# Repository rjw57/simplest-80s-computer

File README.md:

# Experimental repo for retro computing

This is my rough scratch repo where I keep experiments to do with desiging 80s
computer peripherals. It is not in any sensible shape to be used by others yet,
apologies.

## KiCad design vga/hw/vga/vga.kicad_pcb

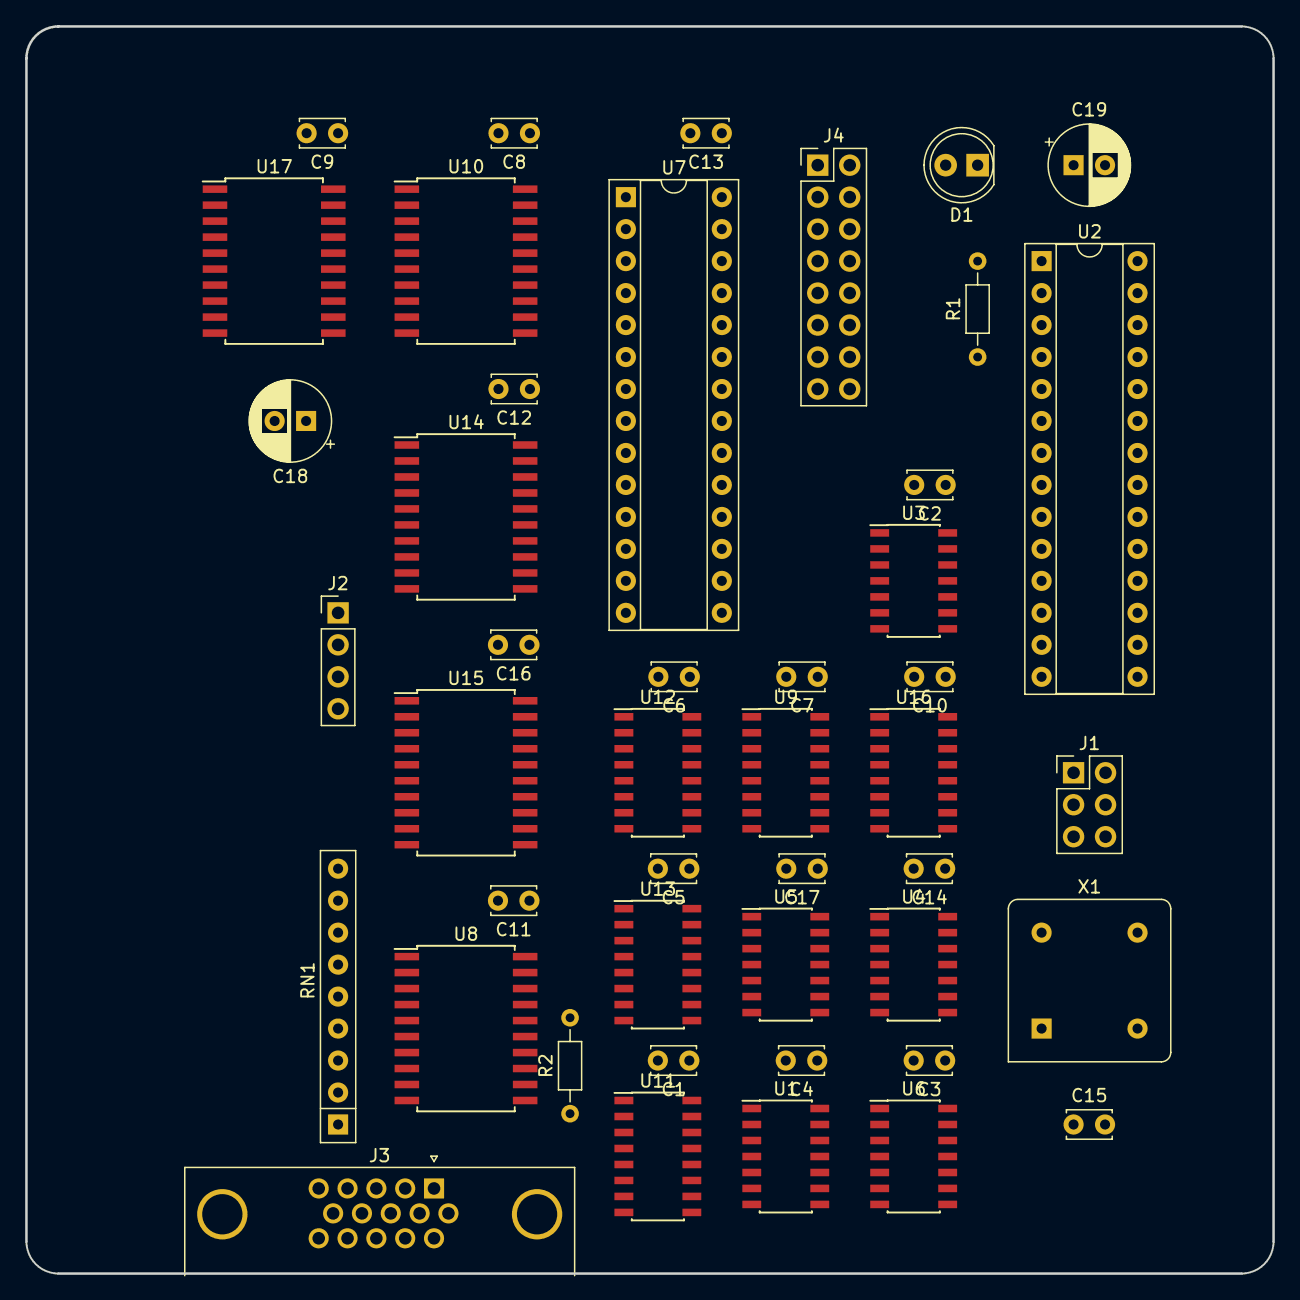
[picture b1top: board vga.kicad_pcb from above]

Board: 2 copper layers, 99.1 x 99.1 mm, 45 parts (0 on the bottom side), 81 nets, no tracks yet.

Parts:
C1, C2, C3, C4, C5, C6, C7, C8, C9, C10, C11, C12, C13, C14, C15, C16, C17: 100n; C_Disc_D3.4mm_W2.1mm_P2.50mm
C18: 10µ; CP_Radial_D6.3mm_P2.50mm
C19: 100µ; CP_Radial_D6.3mm_P2.50mm
D1: LED; LED_D5.0mm
J1: ISP; PinHeader_2x03_P2.54mm_Vertical
J2: PWR; PinHeader_1x04_P2.54mm_Vertical
J3: VGA; DSUB-15-HD_Female_Horizontal_P2.29x1.98mm_EdgePinOffset3.03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
J4: BUS; PinHeader_2x08_P2.54mm_Vertical
R1: 470R; R_Axial_DIN0204_L3.6mm_D1.6mm_P7.62mm_Horizontal
R2: 100R; R_Axial_DIN0204_L3.6mm_D1.6mm_P7.62mm_Horizontal
RN1: R_Network08; R_Array_SIP9
U1, U5, U6: 74HC74; SOIC-14_3.9x8.7mm_P1.27mm
U2: ATmega328-PU; DIP-28_W7.62mm_Socket
U3: 74HC00; SOIC-14_3.9x8.7mm_P1.27mm
U4: 74HC04; SOIC-14_3.9x8.7mm_P1.27mm
U7: CY7C199; DIP-28_W7.62mm_Socket
U8: 74HC245; SOIC-20W_7.5x12.8mm_P1.27mm
U9: 74HC161; SOIC-16_3.9x9.9mm_P1.27mm
U10, U14, U15, U17: 74HC574; SOIC-20W_7.5x12.8mm_P1.27mm
U11: 74HC166; SOIC-16_3.9x9.9mm_P1.27mm
U12, U13: 74HC590; SOIC-16_3.9x9.9mm_P1.27mm
U16: 74LS138; SOIC-16_3.9x9.9mm_P1.27mm
X1: DOTCLK; Oscillator_DIP-8

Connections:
+5V: C1.1, C2.1, C3.1, C4.1, C5.1, C6.1, C7.1, C8.1, C9.1, C10.1, C11.1, C12.1, C13.1, C14.1, C15.1, C16.1, C17.1, C18.1, C19.1, D1.2, J1.2, J2.1, J2.4, J4.2, R1.1, U1.1, U1.4, U1.10, U1.13, U1.14, U2.7, U2.20, U2.21, U3.14, U4.14, U5.1, U5.4, U5.10, U5.14, U6.1, U6.4, U6.10, U6.12, U6.14, U7.28, U8.20, U9.3, U9.6, U9.7, U9.10, U9.16, U10.20, U11.9, U11.16, U12.16, U13.16, U14.20, U15.20, U16.6, U16.16, U17.20, X1.1, X1.8
/A0: J4.4, U16.1
/A1: J4.6, U16.2
/C0: U7.21, U10.19, U12.15
/C1: U7.23, U10.18, U12.1
/C2: U7.24, U10.17, U12.2
/C3: U7.25, U10.16, U12.3
/C4: U7.26, U10.15, U12.4
/C5: U7.1, U10.14, U12.5
/CDOT0: U5.11, U9.14
/CDOT1: U5.3, U9.13
/CDOT2: U5.2, U9.12
/D0: J4.1, U10.2, U14.2, U15.2, U17.19
/D1: J4.3, U10.3, U14.3, U15.3, U17.18
/D2: J4.5, U10.4, U14.4, U15.4, U17.17
/D3: J4.7, U10.5, U14.5, U15.5, U17.16
/D4: J4.9, U10.6, U14.6, U15.6, U17.15
/D5: J4.11, U10.7, U14.7, U15.7, U17.14
/D6: J4.13, U10.8, U14.8, U15.8, U17.13
/D7: J4.15, U10.9, U14.9, U15.9, U17.12
/DOTCLK: U1.3, U4.6, U9.2, U11.7, U12.13, U13.13
/EXTEN: U3.2, U5.6, U5.13, U6.3, U12.14, U13.14
/EXTWREN: U3.5, U5.9
/HSYNC: J3.13, U4.2
/MCUCLK: U1.5, U2.9
/MISO: J1.1, U2.18
/MOSI: J1.4, U2.17
/R0: U7.2, U10.13, U12.7
/R1: U7.3, U10.12, U13.15
/R2: U7.4, U13.1, U14.19
/R3: U7.5, U13.2, U14.18
/R4: U7.6, U13.3, U14.17
/R5: U7.7, U13.4, U14.16
/R6: U7.8, U13.5, U14.15
/R7: U7.9, U13.6, U14.14
/R8: U7.10, U13.7, U14.13
/SCK: J1.3, U2.19
/V0: RN1.9, U8.2, U11.14
/V1: RN1.8, U8.3, U11.12
/V2: RN1.7, U8.4, U11.11
/V3: RN1.6, U8.5, U11.10
/V4: RN1.5, U8.6, U11.5
/V5: RN1.4, U8.7, U11.4
/V6: RN1.3, U8.8, U11.3
/V7: RN1.2, U8.9, U11.2
/VD0: U7.11, U8.18, U15.19, U17.2
/VD1: U7.12, U8.17, U15.18, U17.3
/VD2: U7.13, U8.16, U15.17
/VD3: U7.15, U8.15, U15.16
/VD4: U7.16, U8.14, U15.15, U17.6
/VD5: U7.17, U8.13, U15.14, U17.7
/VD6: U7.18, U8.12, U15.13, U17.8
/VD7: U7.19, U8.11, U15.12, U17.9
/VRAMOE: U3.3, U4.9, U15.1
/VRAMWREN: U3.1, U3.4, U6.5
/VSYNC: J3.14, U4.4
/WRPENDING: U6.2, U6.9
/~CSTART: U9.9, U9.11, U11.15, U12.11
/~EXTEN: U5.5, U10.1, U14.1
/~EXTWREN: U5.8, U5.12, U17.11
/~HSYNC: U1.11, U2.11, U4.1
/~ISPRST: J1.5, R1.2, U2.1
/~RD: J4.8, U17.1
/~RSTCOUNT: U3.8, U9.1, U12.10, U13.10
/~VIS: U2.5, U8.19, U12.12
/~VRAMOE: U4.8, U7.22
/~VRAMWE: U3.6, U7.27
/~VRAMWREN: U6.6, U6.13
/~VSYNC: U1.12, U2.16, U3.10, U4.3
/~WR: J4.10, U16.5
/~WRDATA: U6.11, U15.11, U16.13
/~WRHADDR: U14.11, U16.14
/~WRLADDR: U10.11, U16.15
GND: C1.2, C2.2, C3.2, C4.2, C5.2, C6.2, C7.2, C8.2, C9.2, C10.2, C11.2, C12.2, C13.2, C14.2, C15.2, C16.2, C17.2, C18.2, C19.2, J1.6, J2.2, J2.3, J3.0, J3.5, J3.6, J3.7, J3.8, J3.9, J3.10, J4.12, J4.14, J4.16, RN1.1, U1.7, U2.8, U2.22, U3.7, U4.7, U5.7, U6.7, U7.14, U7.20, U8.1, U8.10, U9.4, U9.5, U9.8, U10.10, U11.1, U11.6, U11.8, U12.8, U13.8, U13.12, U14.10, U15.10, U16.3, U16.4, U16.8, U17.10, X1.4
unnamed: D1.1, U2.2
unnamed: J3.1, J3.2, J3.3, R2.1
unnamed: R2.2, U11.13
unnamed: U1.2, U1.6
unnamed: U1.8, U3.9
unnamed: U4.5, X1.5
unnamed: U12.9, U13.11

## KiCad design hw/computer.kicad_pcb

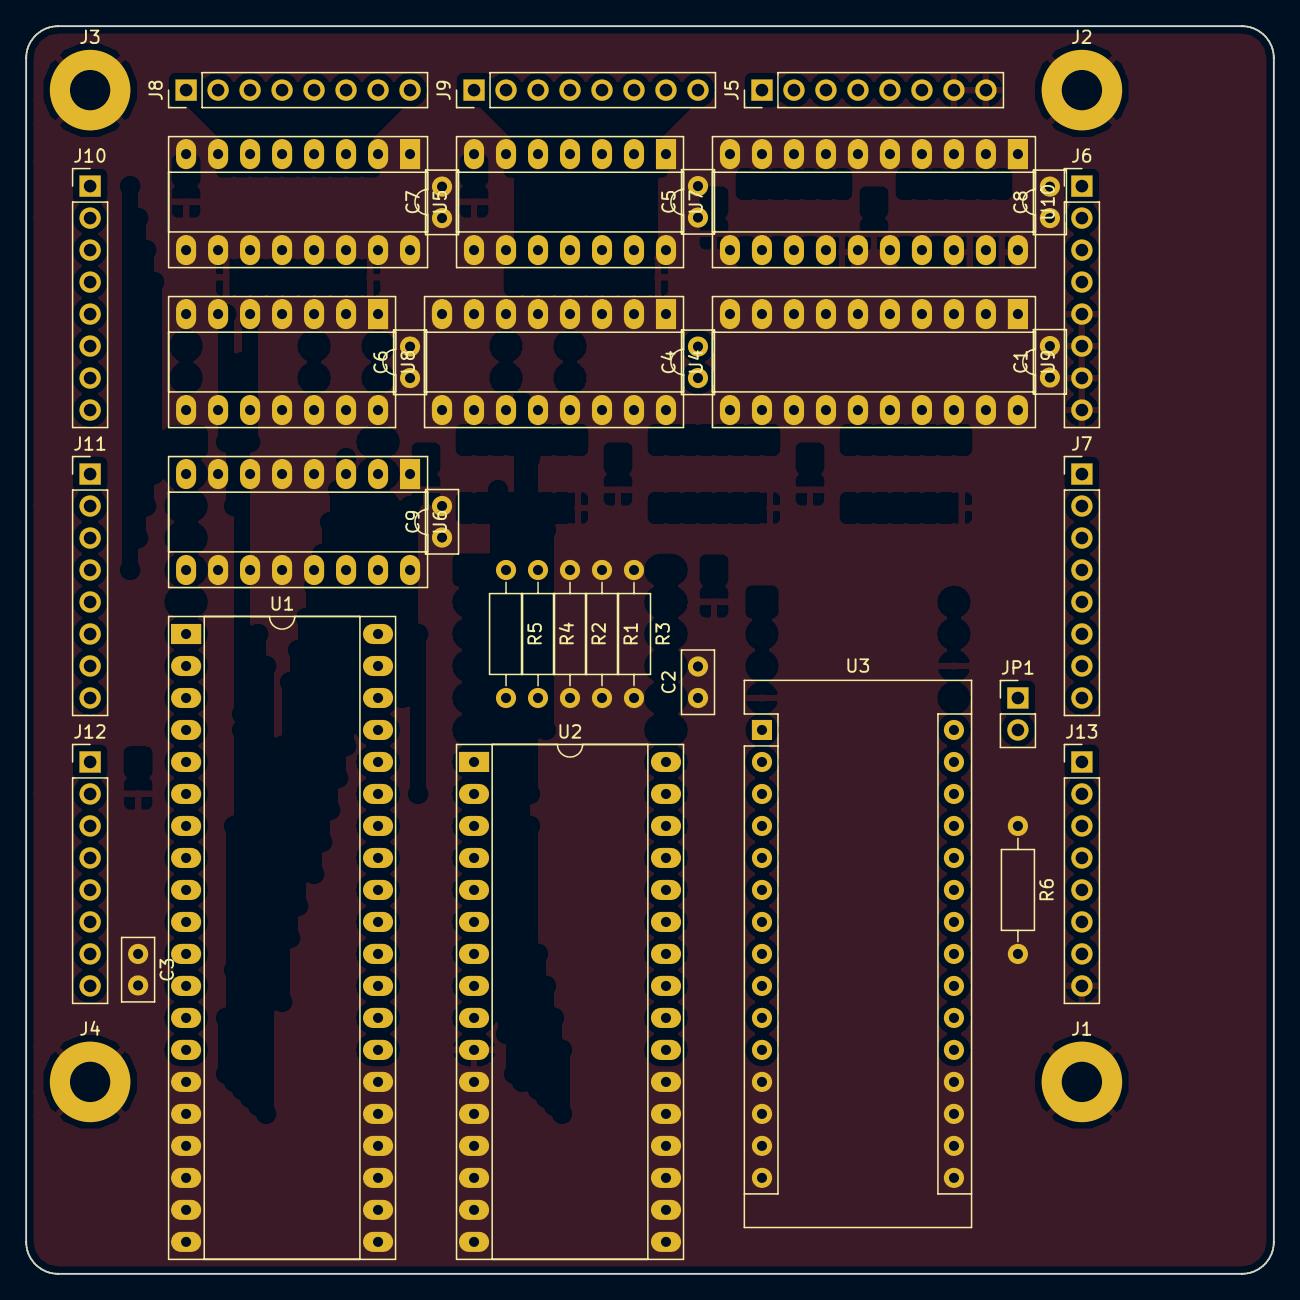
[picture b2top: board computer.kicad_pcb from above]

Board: 2 copper layers, 99.1 x 99.1 mm, 39 parts (0 on the bottom side), 71 nets, no tracks yet.

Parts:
C1, C2, C3, C4, C5, C6, C7, C8, C9: 100n; C_Disc_D5.0mm_W2.5mm_P2.50mm
J1, J2, J3, J4: MOUNT; MountingHole_3.2mm_M3_Pad
J5: POWER; Pin_Header_Straight_1x08_Pitch2.54mm
J6: PORTA; Pin_Header_Straight_1x08_Pitch2.54mm
J7: PORTB; Pin_Header_Straight_1x08_Pitch2.54mm
J8: ADDR2; Pin_Header_Straight_1x08_Pitch2.54mm
J9: ADDR1; Pin_Header_Straight_1x08_Pitch2.54mm
J10: DATA; Pin_Header_Straight_1x08_Pitch2.54mm
J11: CPU1; Pin_Header_Straight_1x08_Pitch2.54mm
J12: CPU2; Pin_Header_Straight_1x08_Pitch2.54mm
J13: NANO; Pin_Header_Straight_1x08_Pitch2.54mm
JP1: NANO PWR; Pin_Header_Straight_1x02_Pitch2.54mm
R1, R2, R3, R4, R5, R6: 330R; R_Axial_DIN0207_L6.3mm_D2.5mm_P10.16mm_Horizontal
U1: Z84C00; DIP-40_W15.24mm_Socket_LongPads
U2: AS6C4008; DIP-32_W15.24mm_Socket_LongPads
U3: Nano; Arduino_Nano
U4, U5, U6: 74HC595; DIP-16_W7.62mm_Socket_LongPads
U7: 74HC30; DIP-14_W7.62mm_Socket_LongPads
U8: 74HC27; DIP-14_W7.62mm_Socket_LongPads
U9, U10: 74HC573; DIP-20_W7.62mm_Socket_LongPads

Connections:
/A0: J9.8, U1.30, U2.12, U4.15, U7.1
/A1: J9.7, U1.31, U2.11, U4.1, U7.2
/A2: J9.6, U1.32, U2.10, U4.2, U7.3
/A3: J9.5, U1.33, U2.9, U4.3, U7.4
/A4: J9.4, U1.34, U2.8, U4.4, U7.5
/A5: J9.3, U1.35, U2.7, U4.5, U7.6
/A6: J9.2, U1.36, U2.6, U4.6, U7.11
/A7: J9.1, U1.37, U2.5, U4.7, U7.12
/A8: J8.8, U1.38, U2.4, U5.15
/A9: J8.7, U1.29, U2.3, U5.1
/A10: J8.6, U1.40, U2.25, U5.2
/A11: J8.5, U1.1, U2.23, U5.3
/A12: J8.4, U1.2, U2.26, U5.4
/A13: J8.3, U1.3, U2.27, U5.5
/A14: J8.2, U1.4, U2.28, U5.6
/A15: J8.1, U1.5, U2.31, U5.7
/Arduino/ARCLK: U3.15, U4.12, U5.12, U6.12
/Arduino/ASCLK: U3.16, U4.11, U5.11, U6.11
/Arduino/ASDA: U3.14, U4.14
/Arduino/~AOE: R6.2, U3.12, U4.13, U5.13, U6.13
/CLK: J12.7, U1.6, U3.11
/D0: J10.1, U1.14, U2.15, U3.19, U9.19, U10.2
/D1: J10.2, U1.15, U2.14, U3.20, U9.18, U10.3
/D2: J10.3, U1.12, U2.13, U3.21, U9.17, U10.4
/D3: J10.4, U1.8, U2.17, U3.22, U9.16, U10.5
/D4: J10.5, U1.7, U2.18, U3.23, U9.15, U10.6
/D5: J10.6, U1.9, U2.19, U3.24, U9.14, U10.7
/D6: J10.7, U1.10, U2.20, U3.9, U9.13, U10.8
/D7: J10.8, U1.13, U2.21, U3.10, U9.12, U10.9
/IO Ports/PA0: J6.1, U10.19
/IO Ports/PA1: J6.2, U10.18
/IO Ports/PA2: J6.3, U10.17
/IO Ports/PA3: J6.4, U10.16
/IO Ports/PA4: J6.5, U10.15
/IO Ports/PA5: J6.6, U10.14
/IO Ports/PA6: J6.7, U10.13
/IO Ports/PA7: J6.8, U10.12
/IO Ports/PB0: J7.1, U9.2
/IO Ports/PB1: J7.2, U9.3
/IO Ports/PB2: J7.3, U9.4
/IO Ports/PB3: J7.4, U9.5
/IO Ports/PB4: J7.5, U9.6
/IO Ports/PB5: J7.6, U9.7
/IO Ports/PB6: J7.7, U9.8
/IO Ports/PB7: J7.8, U9.9
/IO Ports/WRPA: U8.8, U10.11
/IO Ports/~ADDR0: U7.8, U8.10, U8.13
/IO Ports/~RDPB: U8.6, U9.1, U9.11
/~BUSAK: J11.6, U1.23
/~BUSRQ: J12.6, R1.2, U1.25
/~HALT: J11.1, U1.18
/~INT: J12.2, R5.2, U1.16
/~IORQ: J11.3, U1.20, U6.3, U8.2, U8.9
/~M1: J11.7, U1.27
/~MREQ: J11.2, U1.19, U2.22, U6.2
/~NMI: J12.3, R4.2, U1.17
/~RD: J11.4, U1.21, U2.24, U6.15, U8.1
/~RESET: J12.4, R3.2, U1.26, U3.7
/~RFSH: J11.8, U1.28
/~WAIT: J12.5, R2.2, U1.24
/~WR: J11.5, U1.22, U2.29, U6.1, U8.11
GND: C1.2, C2.2, C3.2, C4.2, C5.2, C6.2, C7.2, C8.2, C9.2, J1.1, J2.1, J3.1, J4.1, J5.5, J5.6, J5.7, J5.8, J12.8, J13.7, J13.8, U2.16, U3.4, U3.28, U4.8, U5.8, U6.8, U7.7, U8.4, U8.5, U8.7, U9.10, U10.1, U10.10
unnamed: J13.1, J13.2, JP1.1, U3.27
unnamed: J13.3, U3.5
unnamed: J13.4, U3.6
unnamed: J13.5, U3.8
unnamed: J13.6, U3.13
unnamed: U4.9, U5.14
unnamed: U5.9, U6.14
unnamed: U8.3, U8.12
VCC: C1.1, C2.1, C3.1, C4.1, C5.1, C6.1, C7.1, C8.1, C9.1, J5.1, J5.2, J5.3, J5.4, J12.1, JP1.2, R1.1, R2.1, R3.1, R4.1, R5.1, R6.1, U1.11, U2.1, U2.2, U2.30, U2.32, U4.10, U4.16, U5.10, U5.16, U6.10, U6.16, U7.14, U8.14, U9.20, U10.20

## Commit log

2018-04-15 initial import
2018-05-28 draft of VGA controller
2018-06-04 update VGA to latest version
2018-06-09 re-worked timings
    Now AVR generates HSYNC, VSYNC and VIS itself using timers with no
    external circuitry!
2018-06-09 move to 512x384 output resolution
    By halving 1024x768 we can nicely separate row and column bits which
    will simplify circuitry.
2018-07-07 working version again
2018-07-08 remove wait time
2018-07-08 add font dir
2018-07-08 add font demo
2018-07-08 add random character display
2018-07-08 removed old schematic and update fw
2018-07-08 add README
2018-07-08 update schematic
2018-07-09 update read/write support with scrolling demo
2018-07-09 tweak timing of demo to make it a little quicker
2018-07-10 timings.c: disable waiting on WAITB
2018-07-10 added tidied up schematic
2018-07-15 start sketching out vga scheatic in kicad
2018-07-21 start to transfer schematic to kicad
2018-07-21 add RAM in
2018-07-21 add bus interface header
2018-07-28 flesh out PCB
